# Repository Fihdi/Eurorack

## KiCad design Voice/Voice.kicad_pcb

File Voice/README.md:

# Full Synthesizer Voice with Envelope Generator

The Envelope generator is my original decay generator with an instant attack and voltage controllable decay time. The accent can also be controlled via CV. The decay signal can modulate the other three sections with variable strengths or be used independantly.

The VCO is a triangle-core, OTA based VCO, same as in the TRIVCO. The sub-oscillator is created by feeding the pulse output of the VCO into a 4040 counter IC to create another square-wave output at half the frequency. The Sub output and the PWM signal are summed together, the strenght of the SUB output can be controlled with the SUB knob. Turning "PWM" all the way to the max/min turns the original square wave signal off by setting the duty cycle to 0% or 100%. 

The VCF section used to be a AS3350 circuit. It worked, but I was not happy with the sound of it, I was hoping for squelchy, acid like sounds, which I couldnt get out of it the way I wanted. I decided to adapt the existing VCF PCB so it can be slotted into the backside of the module.

The VCA is the VCA-3 by Rene Schmitz, the same that I use for my percussion modules like Hat, Bell or Fold, it is an incredibly reliable circuit. It is DC biased so modulating CV is possible. 

When building this module, normalize the Square wave output to the IN jack of the VCF and normalize the LP output to the IN of the VCA.

I am thinking about making another version of this Module featuring a synch-able LFO instead of the envelope and maybe adding a Noise OUT as well. 

The module that you see in the picture above is using circuit boards that were fabricated by [PCBWay](https://www.pcbway.com). This is the biggest set of PCBs in terms of size, being 20 hp in width, that I ordered and they all worked flawlessly the first time! They have excellent build quality and I can recommend using their service to build your own projects! I used the "Black" option for the soldermask and the surface has very deep and glossy black finish, which looks amazing, they also have an option for a "Matte Black" finish which I will try next time. Thank you PCBWay for sponsoring this module.

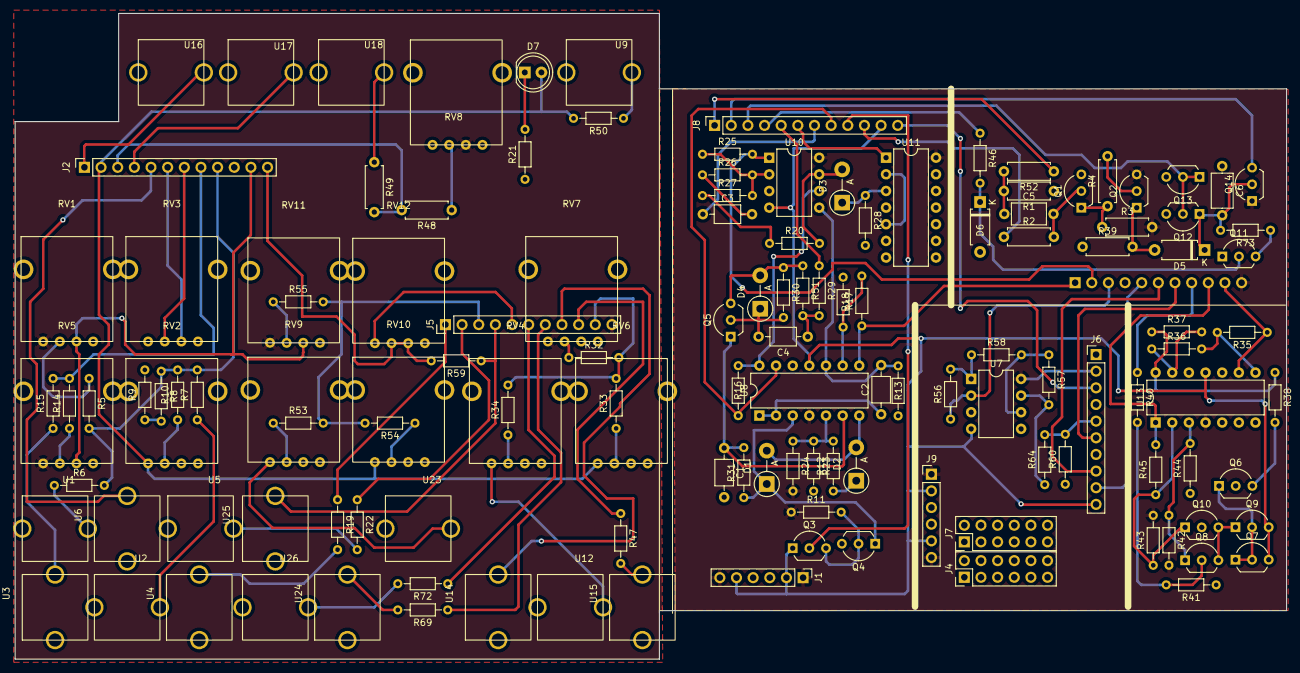
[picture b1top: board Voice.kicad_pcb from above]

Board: 2 copper layers, 194.0 x 98.5 mm, 134 parts (1 on the bottom side), 86 nets.

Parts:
C1, C2, C3, C4: C; C_Axial_L3.8mm_D2.6mm_P7.50mm_Horizontal
C5, C6: 5n; C_Axial_L5.1mm_D3.1mm_P7.50mm_Horizontal
D1, D2, D3, D4: D; D_DO-15_P5.08mm_Vertical_AnodeUp
D5, D6: D; D_A-405_P7.62mm_Horizontal
D7: LED; LED_D5.0mm
J1, J9: Conn_01x06_Pin; PinHeader_1x06_P2.54mm_Vertical
J2, J8: Conn_01x12_Pin; PinSocket_1x12_P2.54mm_Vertical
J3: Conn_01x11_Pin; PinSocket_1x11_P2.54mm_Vertical
J4, J7: Conn_02x06_Odd_Even; PinHeader_2x06_P2.54mm_Vertical
J5: Conn_01x11_Pin; PinHeader_1x11_P2.54mm_Vertical
J6: Conn_01x10_Pin; PinHeader_1x10_P2.54mm_Vertical
Q1, Q12, Q13, Q14: BC547; TO-92L_Inline_Wide
Q2, Q11: BC557; TO-92L_Inline_Wide
Q3, Q6: BC557; TO-92_Inline_Wide
Q4, Q5, Q7, Q8, Q9, Q10: BC547; TO-92_Inline_Wide
R1, R2, R3, R39, R48, R49: 100k; R_Axial_DIN0207_L6.3mm_D2.5mm_P7.62mm_Horizontal
R4, R52: 10k; R_Axial_DIN0207_L6.3mm_D2.5mm_P7.62mm_Horizontal
R5, R6, R7, R10, R23, R24, R25, R26, R28, R32, R33, R34, R35, R38, R40, R53, R54, R55, R56, R57, R58, R59: 100k; R_Axial_DIN0204_L3.6mm_D1.6mm_P7.62mm_Horizontal
R8, R36, R37, R46, R47, R50, R60, R69, R72, R73: 1k; R_Axial_DIN0204_L3.6mm_D1.6mm_P7.62mm_Horizontal
R9: 1k TRIMM; R_Axial_DIN0204_L3.6mm_D1.6mm_P7.62mm_Horizontal
R11: 1M; R_Axial_DIN0204_L3.6mm_D1.6mm_P7.62mm_Horizontal
R12, R29, R30, R51, R64: 10k; R_Axial_DIN0204_L3.6mm_D1.6mm_P7.62mm_Horizontal
R13, R14, R15, R16, R17, R18, R19, R22: R; R_Axial_DIN0204_L3.6mm_D1.6mm_P7.62mm_Horizontal
R20: 0R; R_Axial_DIN0204_L3.6mm_D1.6mm_P7.62mm_Horizontal
R21: 2k2; R_Axial_DIN0204_L3.6mm_D1.6mm_P7.62mm_Horizontal
R27, R44, R45: 200k; R_Axial_DIN0204_L3.6mm_D1.6mm_P7.62mm_Horizontal
R31: MAX 1k (optional); R_Axial_DIN0204_L3.6mm_D1.6mm_P7.62mm_Horizontal
R41: 200R; R_Axial_DIN0204_L3.6mm_D1.6mm_P7.62mm_Horizontal
R42, R43: 50k; R_Axial_DIN0204_L3.6mm_D1.6mm_P7.62mm_Horizontal
RV1, RV2, RV3, RV4, RV5, RV6, RV7, RV8, RV9, RV10, RV11, RV12: R_Potentiometer; AlpsPot
U1, U2, U3, U4, U5, U6, U9, U12, U14, U15, U16, U17, U18, U23, U24, U25, U26: Aux_flush; 3mm5 Mono Aux
U7, U10: TL072; DIP-8_W7.62mm
U8, U13: TL074; DIP-14_W7.62mm
U11: 4013; DIP-14_W7.62mm

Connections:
+12V: J1.1, J1.6, J3.11, J5.11, J6.2, J9.1, J9.6, Q2.3 (E), Q14.1 (C), R3.2, R11.1, R24.2, R42.2, R43.2, RV1.1, RV5.1, RV7.1, RV8.3, RV11.1, U7.8 (V+), U8.4 (V+), U10.8 (V+), U11.14 (VDD), U13.4 (V+)
-12V: J1.2, J1.5, J2.11, J6.10, J8.11, J9.2, J9.5, Q3.1 (C), Q7.3 (E), Q9.3 (E), RV1.3, RV5.3, RV11.3, U7.4 (V-), U8.11 (V-), U10.4 (V-), U13.11 (V-)
ACC: J2.4, J8.4, R46.1, U17.1
BP: J3.6, J5.6, J6.8, R72.1
CVFIN: J3.4, J5.4, R59.1, U25.1
DECAY: J2.3, J8.3, Q12.2 (B), Q13.1 (C), Q13.2 (B), R48.2, R49.2
DFF: J2.6, J8.6, RV3.3, U11.1 (Q)
ENV: D7.2 (A), J2.2, J8.2, Q14.3 (E), R50.2, RV2.1, RV6.1, RV10.1
GND: C1.2, C6.1, D4.2 (A), D6.2 (A), J1.3, J1.4, J2.10, J6.1, J8.10, J9.3, J9.4, Q1.3 (E), Q4.3 (E), Q5.3 (E), Q6.2 (B), Q10.2 (B), Q11.1 (C), Q12.3 (E), Q13.3 (E), R1.1, R2.1, R9.2, R13.2, R18.2, R21.1, R23.2, R28.2, R30.1, R39.1, R41.1, R44.1, R51.1, R60.1, RV2.3, RV3.1, RV4.3, RV6.3, RV7.3, RV8.1, RV9.3, RV10.3, U7.3 (+), U7.5 (+), U8.12 (+), U10.3 (+), U11.4 (R), U11.6 (S), U11.7 (VSS), U13.10 (+), U13.12 (+)
LP: J3.7, J5.7, J6.6, R69.1
unnamed: C3.2, R26.1
unnamed: C4.1, R29.2, R51.2
unnamed: C5.1, R1.2, R52.2
unnamed: D1.2 (A), D2.2 (A), U8.7
unnamed: D1.1 (K), Q4.1 (C), R31.1, U8.3 (+)
unnamed: D2.1 (K), R12.1
unnamed: D3.2 (A), R20.2, U10.7
unnamed: D3.1 (K), R28.1, U11.3 (C)
unnamed: C4.2, D4.1 (K), Q5.2 (B), R30.2
unnamed: D5.2 (A), Q2.1 (C), R39.2
unnamed: C6.2, D5.1 (K), Q12.1 (C), Q14.2 (B), R73.2
unnamed: D6.1 (K), Q11.2 (B), R46.2
unnamed: D7.1 (K), R21.2
unnamed: C5.2, Q1.2 (B), R2.2
unnamed: Q1.1 (C), R3.1, R4.1
unnamed: Q2.2 (B), R4.2
unnamed: Q3.3 (E), Q4.2 (B), R11.2
unnamed: C1.1, Q5.1 (C), R31.2, U8.6 (-)
unnamed: Q6.1 (C), Q7.1 (C), Q7.2 (B), Q9.2 (B)
unnamed: Q6.3 (E), R38.2
unnamed: Q8.2 (B), R40.2, R41.2
unnamed: Q8.1 (C), R42.1, R44.2, U13.3 (+)
unnamed: Q10.1 (C), R43.1, R45.1, U13.2 (-)
unnamed: Q8.3 (E), Q9.1 (C), Q10.3 (E)
unnamed: Q11.3 (E), R73.1
unnamed: R5.1, RV1.2
unnamed: R6.1, U1.1
unnamed: R7.1, U2.1
unnamed: R8.2, R9.1
unnamed: R10.1, RV2.2
unnamed: R14.1, RV5.2
unnamed: R15.1, U3.1
unnamed: R19.2, U4.1
unnamed: R20.1, R27.1
unnamed: R22.2, U5.1
unnamed: R32.1, RV7.2
unnamed: R33.1, RV6.2
unnamed: R34.1, RV4.2
unnamed: R35.2, R36.2, U13.8
unnamed: R37.1, R38.1, U13.14
unnamed: R47.2, U15.1
unnamed: R48.1, RV8.2
unnamed: R49.1, U18.1
unnamed: R50.1, U9.1
unnamed: R53.1, RV9.2
unnamed: R54.1, RV10.2
unnamed: R55.1, RV11.2
unnamed: R56.2, R58.1, U7.1
unnamed: R57.2, R64.1, U7.7
unnamed: R69.2, U24.1
unnamed: R72.2, U26.1
unnamed: RV4.1, U12.1
unnamed: RV9.1, U23.1
unnamed: R57.1, R58.2, U7.6 (-)
unnamed: C2.1, U8.1, U8.2 (-)
unnamed: R12.2, R23.1, R24.1, U8.5 (+)
unnamed: R17.2, R18.1, U8.9 (-)
unnamed: R25.1, R26.2, R27.2, U10.2 (-)
unnamed: C2.2, R13.1, U8.10 (+), U10.5 (+)
unnamed: R16.2, U8.14, U10.6 (-)
unnamed: U11.2 (~Q), U11.5 (D)
unnamed: R36.1, R37.2, U13.13 (-)
PWMCV: J2.8, J8.8, R14.2, R15.2, R16.1, U8.13 (-)
RES: J3.5, J5.5, J6.9, RV12.1
SAW: J3.1, J5.1, R17.1, R19.1, U8.8
SQR: J3.2, J5.2, R22.1, R25.2, U10.1
SUB: C3.1, J2.7, J8.7, RV3.2
SYNC: J2.5, J8.5, R29.1, U6.1
TRG: J2.1, J8.1, R52.1, U16.1
TRP: J6.5, R60.2, R64.2
VCACV: J3.10, J5.10, R32.2, R33.2, R34.2, R35.1, U13.9 (-)
VCAIN: J3.8, J5.8, R40.1, U14.1
VCAOUT: J3.9, J5.9, R45.2, R47.1, U13.1
VCFCV: J3.3, J5.3, R53.2, R54.2, R55.2, R56.1, U7.2 (-)
VCOCV: J2.9, J8.9, Q3.2 (B), R5.2, R6.2, R7.2, R8.1, R10.2
VGND2: J2.12, J6.3, J8.12, R59.2, RV12.2, RV12.3

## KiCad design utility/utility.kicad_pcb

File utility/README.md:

Multiple modules on one PCB

Inverse VCO: Turns a frequency into a voltage

-No input hysteresis

Slew Rate Limiter:
-I don't know why but it does not slew when I built it, or at the very least it does not slew very noticably. Maybe just a bigger cap is needed.

Attenuverter:
-No issues but some LEDs would be nice, same for the analog XOR

AXOR (Analog XOR)

A differential amplifier followed by a full wave rectifier.

The transfer function of the CV output is: Vout = |(Vin1 - Vin2)| 

When two square waves of equal amplitude are sent into the inputs, the output is (IN1 XOR IN2), this gives a kind of ringmodulator sound.

Sending a single triangle wave into IN1 or IN2 will rectify it and thus double the freuqency.

Sending two LFOs into the inputs produces a really weird (and fun) signal.

AUD output is Vout followed by a highpass to center it around 0V.

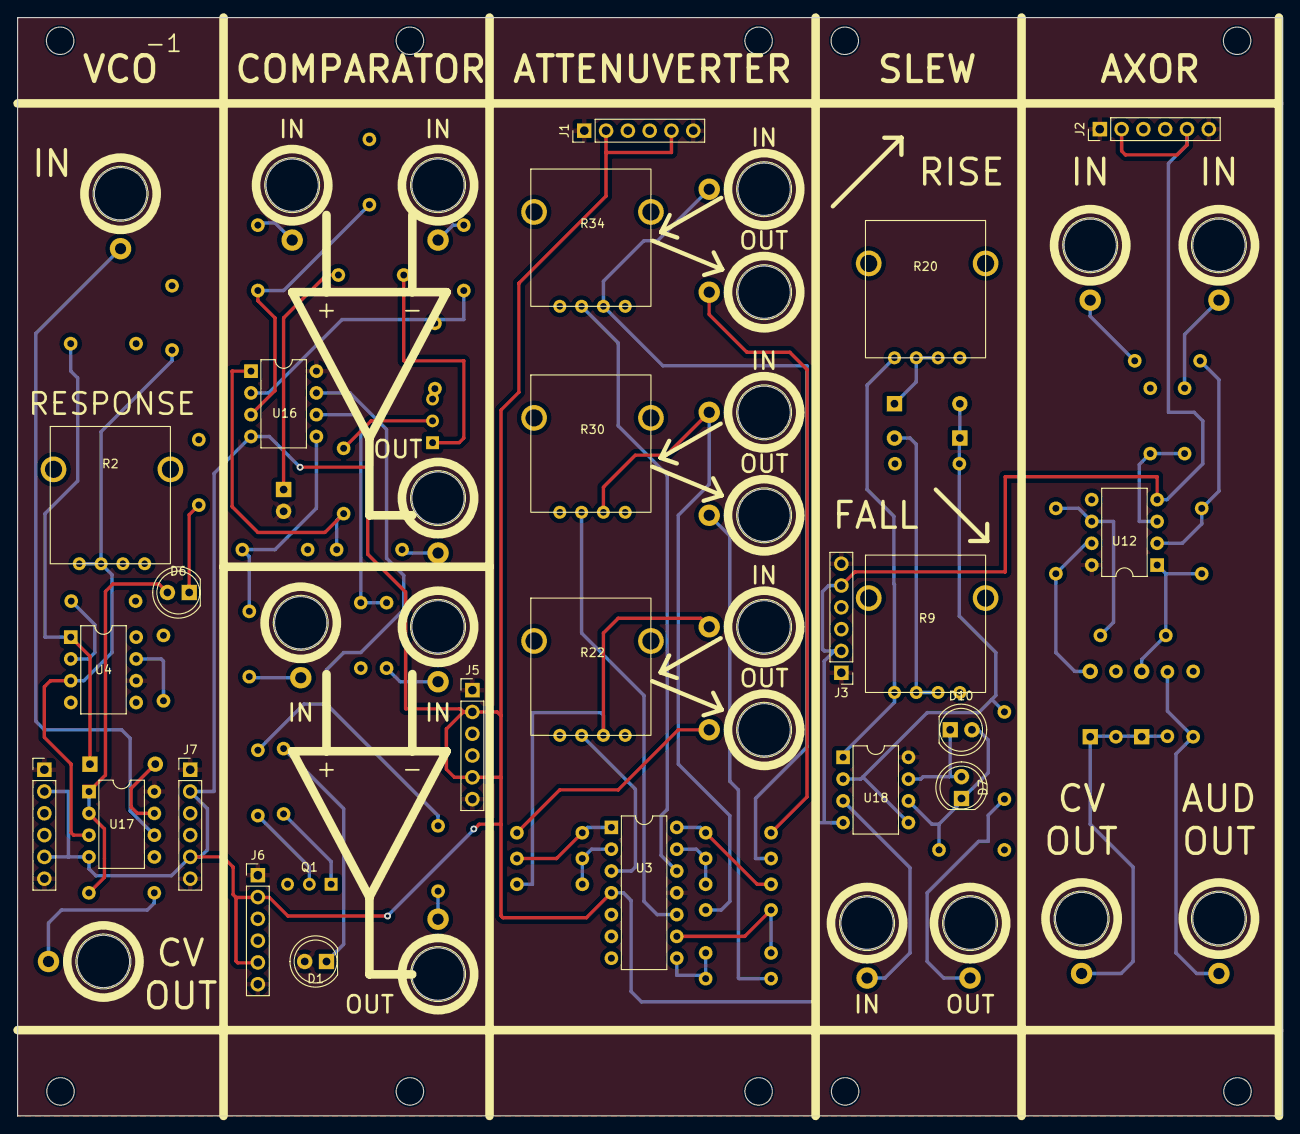
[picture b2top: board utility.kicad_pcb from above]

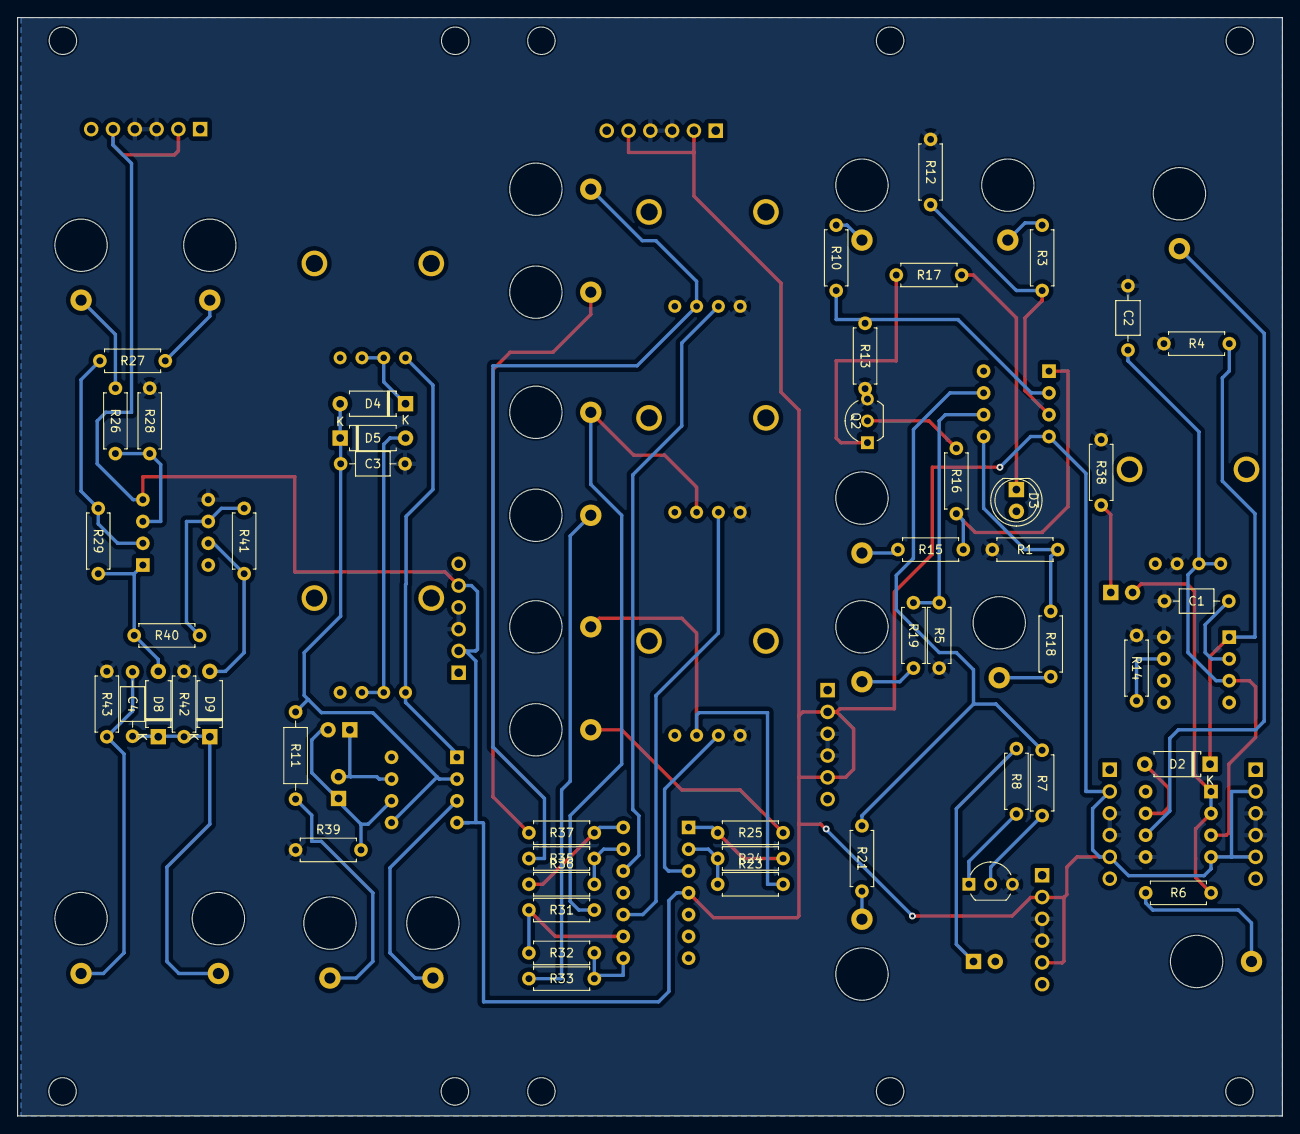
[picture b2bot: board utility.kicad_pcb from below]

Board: 2 copper layers, 147.4 x 128.0 mm, 92 parts (49 on the bottom side), 62 nets.

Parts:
C1, C2, C3, C4: C; C_Axial_L3.8mm_D2.6mm_P7.50mm_Horizontal
D1, D3, D6, D7, D10: LED; LED_D5.0mm
D2, D4, D5, D8, D9: D; D_A-405_P7.62mm_Horizontal
J1, J2, J3, J4, J5, J6, J7: Conn_01x06_Male; PinHeader_1x06_P2.54mm_Vertical
Q1, Q2: BC547; TO-92_Inline_Wide
R1, R3, R4, R5, R6, R7, R8, R10, R12, R13, R14, R15, R16, R17, R18, R19, R21, R23, R24, R25, R26, R27, R28, R29, R31, R32, R33, R35, R36, R37, R38, R39, R40, R41, R42, R43: R; R_Axial_DIN0207_L6.3mm_D2.5mm_P7.62mm_Horizontal
R2, R9, R20, R22, R30, R34: AlpsPot
R11: R; R_Axial_DIN0207_L6.3mm_D2.5mm_P10.16mm_Horizontal
U1, U2, U5, U6, U7, U8, U9, U10, U11, U13, U14, U15, U19, U20, U21, U22, U23, U24, U25, U26: Aux_flush; aux_flush
U3: TL074; DIP-14_W7.62mm
U4: LM2907; DIP-8_W7.62mm
U12, U16, U17, U18: TL072; DIP-8_W7.62mm

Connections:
+12V: D1.2 (A), D3.2 (A), J1.1, J1.6, J2.1, J2.6, J3.1, J3.6, J4.1, J4.6, J5.1, J5.6, J6.1, J6.6, J7.1, J7.6, U3.11 (V-), U4.6, U12.8 (V+), U16.8 (V+), U17.8 (V+), U18.8 (V+)
-12V: J1.2, J1.5, J2.2, J2.5, J3.2, J3.5, J4.2, J4.5, J5.2, J5.5, J6.2, J6.5, J7.2, J7.5, U3.4 (V+), U12.4 (V-), U16.4 (V-), U17.4 (V-), U18.4 (V-)
GND: C1.2, C2.2, C3.2, J1.3, J1.4, J2.3, J2.4, J3.3, J3.4, J4.3, J4.4, J5.3, J5.4, J6.3, J6.4, J7.3, J7.4, Q1.3 (E), Q2.3 (E), R1.1, R2.3 (E), R4.1, R5.1, R12.1, R13.1, R14.1, R22.1 (A), R28.1, R30.1 (A), R34.1 (A), R38.1, R39.1, R42.1, R43.1, U4.8, U12.5 (+), U17.5 (+)
unnamed: C1.1, U4.2
unnamed: C2.1, R2.1 (A), R2.2 (S), U4.3, U17.3 (+)
unnamed: C3.1, D4.2 (A), D5.1 (K), R11.2, U18.2 (-), U18.5 (+)
unnamed: C4.1, D8.1 (K), D9.1 (K), R42.2, U21.1
unnamed: C4.2, R43.2, U26.1
unnamed: D1.1 (K), R8.2
unnamed: D2.1 (K), R4.2, U4.1
unnamed: D2.2 (A), U17.7
unnamed: D3.1 (K), R17.2
unnamed: D4.1 (K), R20.2 (S), R20.3 (E)
unnamed: D5.2 (A), R9.2 (S), R9.3 (E)
unnamed: D6.1 (K), R38.2
unnamed: D7.1 (K), D10.2 (A), R39.2, U18.6 (-)
unnamed: D7.2 (A), D10.1 (K), U18.7
unnamed: D8.2 (A), R29.1, R40.2, U12.1
unnamed: D9.2 (A), R41.1, U12.7
unnamed: Q1.1 (C), R8.1
unnamed: Q1.2 (B), R7.1
unnamed: Q2.1 (C), R17.1
unnamed: Q2.2 (B), R16.1
unnamed: R1.2, R18.1, U16.5 (+)
unnamed: R3.2, U9.1
unnamed: R6.1, U5.1
unnamed: D6.2 (A), R6.2, U17.1, U17.2 (-)
unnamed: R10.1, R13.2, U16.2 (-)
unnamed: R10.2, U8.1
unnamed: R11.1, U7.1
unnamed: R3.1, R12.2, U16.3 (+)
unnamed: R14.2, U4.7
unnamed: R15.1, U14.1
unnamed: R15.2, R16.2, U16.1
unnamed: R18.2, U10.1
unnamed: R5.2, R19.1, U16.6 (-)
unnamed: R19.2, U1.1
unnamed: R9.1 (A), R20.1 (A), U18.1
unnamed: R21.1, U11.1
unnamed: R7.2, R21.2, U16.7
unnamed: R22.2 (S), U3.3 (+)
unnamed: R22.3 (E), R23.2, U13.1
unnamed: R23.1, R24.2, U3.2 (-)
unnamed: R24.1, R25.2, U3.1
unnamed: R25.1, U19.1
unnamed: R26.1, R28.2, U12.3 (+)
unnamed: R26.2, U15.1
unnamed: R27.1, R29.2, U12.2 (-)
unnamed: R27.2, U20.1
unnamed: R30.2 (S), U3.10 (+)
unnamed: R30.3 (E), R31.2, U22.1
unnamed: R31.1, R32.2, U3.9 (-)
unnamed: R32.1, R33.2, U3.8
unnamed: R33.1, U23.1
unnamed: R34.2 (S), U3.12 (+)
unnamed: R34.3 (E), R35.2, U24.1
unnamed: R35.1, R36.2, U3.13 (-)
unnamed: R36.1, R37.2, U3.14
unnamed: R37.1, U25.1
unnamed: R40.1, R41.2, U12.6 (-)
unnamed: U2.1, U17.6 (-)
unnamed: U6.1, U18.3 (+)
